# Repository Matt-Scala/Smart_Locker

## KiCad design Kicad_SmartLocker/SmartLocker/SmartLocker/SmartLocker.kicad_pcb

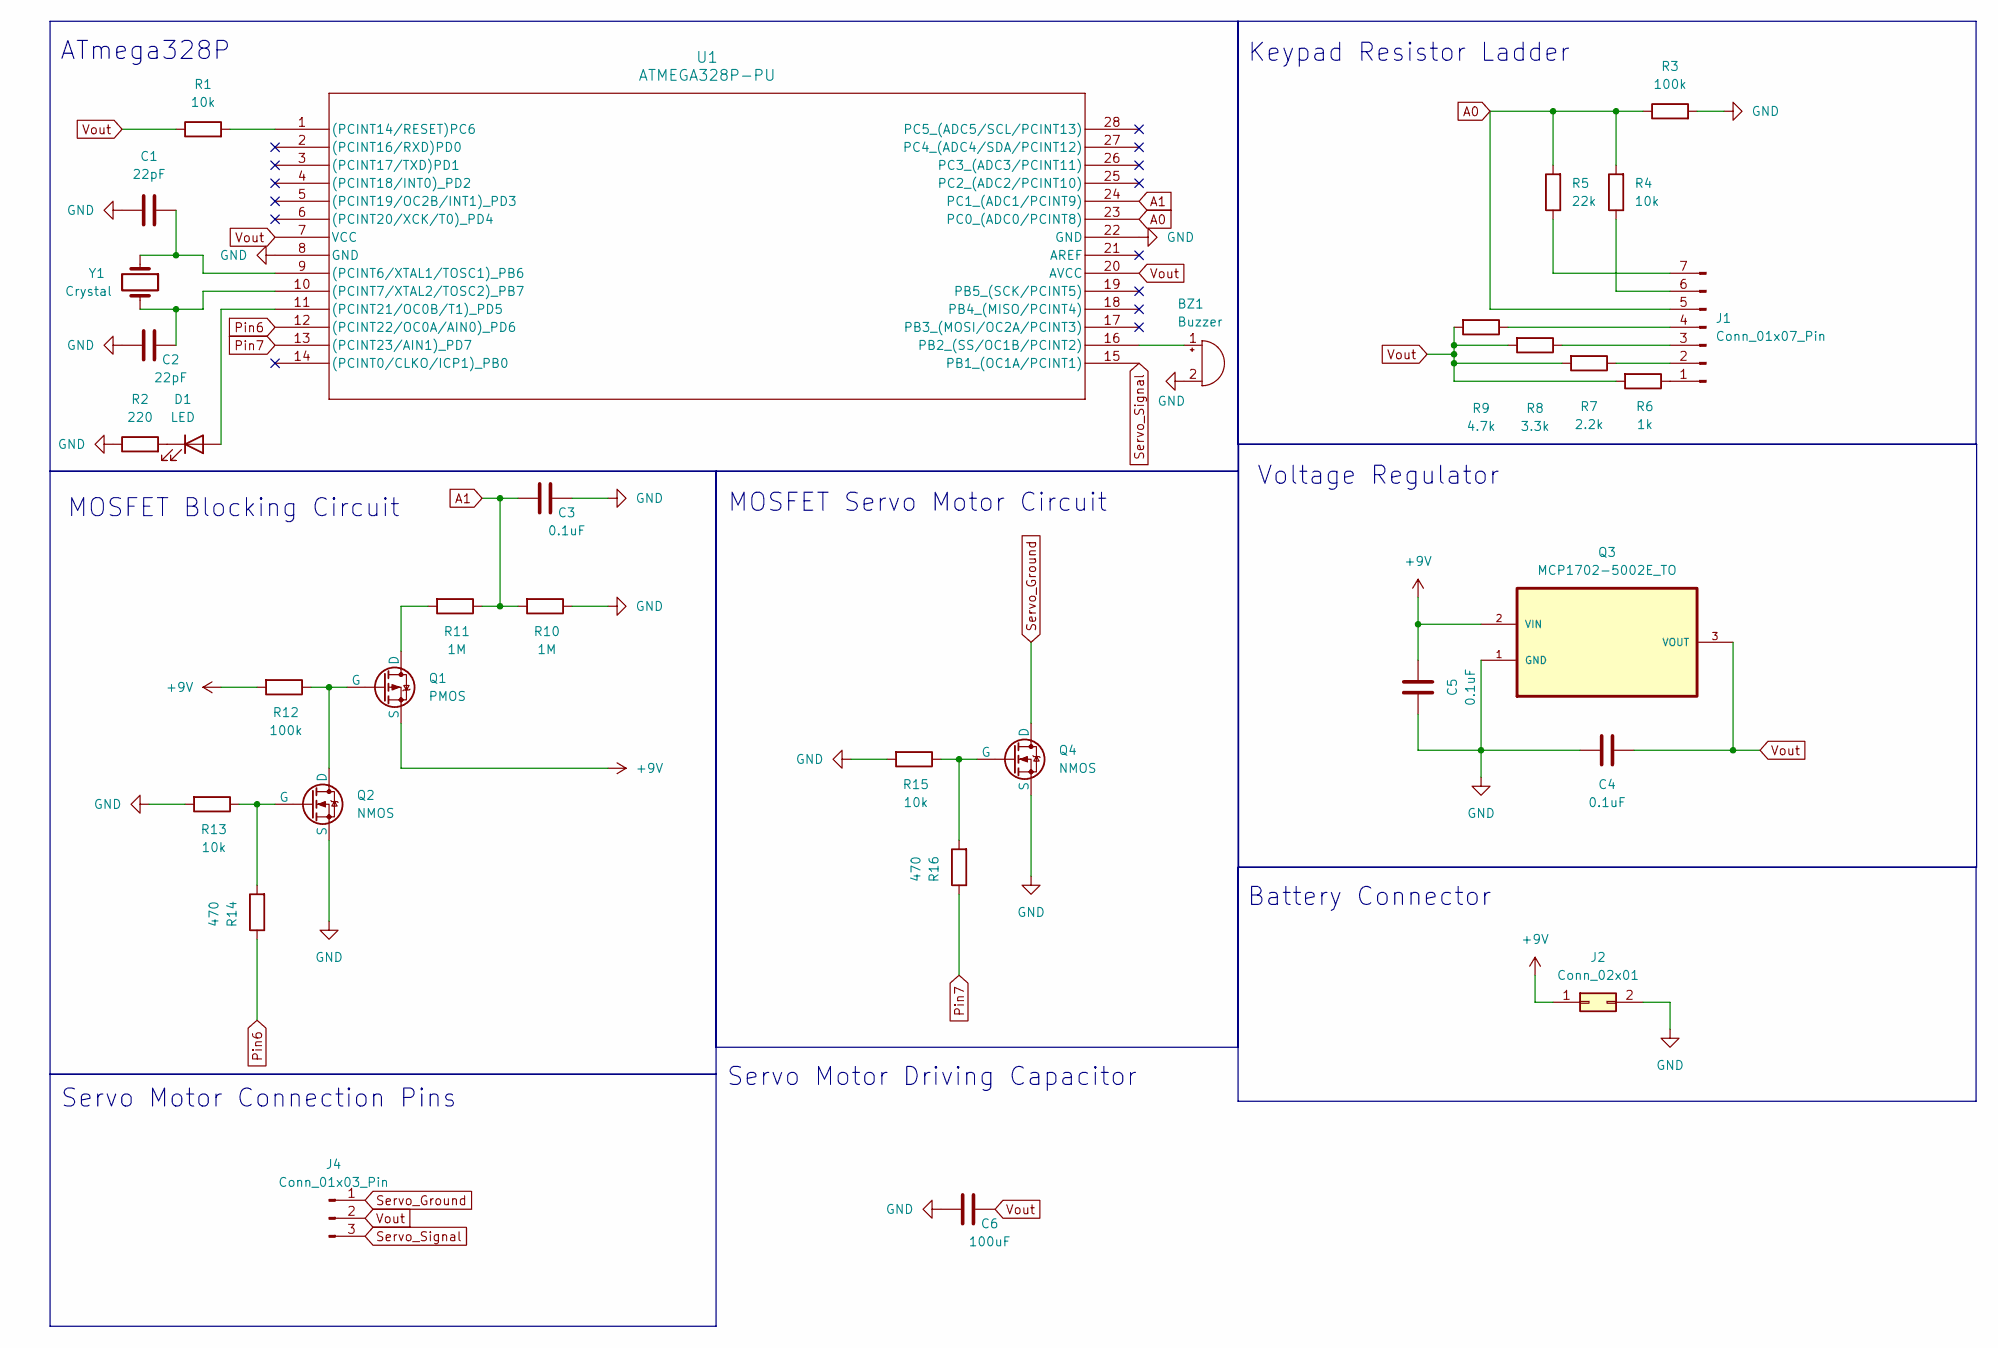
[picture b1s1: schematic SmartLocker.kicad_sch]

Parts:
BZ1: Buzzer; CUI_CMI-1275C-050
C1, C2: 22pF; C_Disc_D4.3mm_W1.9mm_P5.00mm_Handsolder
C3, C4, C5: 0.1uF; C_Disc_D4.3mm_W1.9mm_P5.00mm_Handsolder
C6: 100uF; C_Radial_D8.0mm_H7.0mm_P3.50mm
D1: LED; LED_D3.0mm
J1: Conn_01x07_Pin; PinSocket_1x07_P2.54mm_Vertical
J2: Conn_02x01; BatteryConnector
J4: Conn_01x03_Pin; PinSocket_1x03_P2.54mm_Vertical
Q1: PMOS; TO-92_HandSolder
Q2, Q4: NMOS; TO-92_HandSolder
Q3: MCP1702-5002E_TO; MCP1702 TO-92; MPN MCP1702-5002E/TO
R1, R4, R13, R15: 10k; R_Axial_DIN0309_L9.0mm_D3.2mm_P12.70mm_Horizontal
R2: 220; R_Axial_DIN0309_L9.0mm_D3.2mm_P12.70mm_Horizontal
R3, R12: 100k; R_Axial_DIN0309_L9.0mm_D3.2mm_P12.70mm_Horizontal
R5: 22k; R_Axial_DIN0309_L9.0mm_D3.2mm_P12.70mm_Horizontal
R6: 1k; R_Axial_DIN0309_L9.0mm_D3.2mm_P12.70mm_Horizontal
R7: 2.2k; R_Axial_DIN0309_L9.0mm_D3.2mm_P12.70mm_Horizontal
R8: 3.3k; R_Axial_DIN0309_L9.0mm_D3.2mm_P12.70mm_Horizontal
R9: 4.7k; R_Axial_DIN0309_L9.0mm_D3.2mm_P12.70mm_Horizontal
R10, R11: 1M; R_Axial_DIN0207_L6.3mm_D2.5mm_P10.16mm_Horizontal
R14, R16: 470; R_Axial_DIN0207_L6.3mm_D2.5mm_P10.16mm_Horizontal
U1: ATMEGA328P-PU; ATmega328P
Y1: Crystal; Crystal_HC49-4H_Vertical

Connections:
+9V: C5.2, J2.1, Q1.3 (S), Q3.2 (VIN), R12.2
A0: J1.5, R3.1, R4.2, R5.2, U1.23 (PC0_(ADC0/PCINT8))
A1: C3.1, R10.2, R11.1, U1.24 (PC1_(ADC1/PCINT9))
GND: BZ1.2 (-), C1.1, C2.1, C3.2, C4.1, C5.1, C6.1, J2.2, Q2.3 (S), Q3.1 (GND), Q4.3 (S), R2.1, R3.2, R10.1, R13.2, R15.2, U1.8 (GND), U1.22 (GND)
unnamed: BZ1.1 (+), U1.16 (PB2_(SS/OC1B/PCINT2))
unnamed: D1.2 (A), U1.11 ((PCINT21/OC0B/T1)_PD5)
unnamed: D1.1 (K), R2.2
unnamed: J1.1, R6.1
unnamed: J1.2, R7.1
unnamed: J1.3, R8.1
unnamed: J1.4, R9.1
unnamed: J1.6, R4.1
unnamed: J1.7, R5.1
unnamed: Q1.1 (D), R11.2
unnamed: Q1.2 (G), Q2.1 (D), R12.1
unnamed: Q2.2 (G), R13.1, R14.2
unnamed: Q4.2 (G), R15.1, R16.2
unnamed: C1.2, U1.9 ((PCINT6/XTAL1/TOSC1)_PB6), Y1.1
unnamed: C2.2, U1.10 ((PCINT7/XTAL2/TOSC2)_PB7), Y1.2
unnamed: R1.2, U1.1 ((PCINT14/RESET)PC6)
Pin6: R14.1, U1.12 ((PCINT22/OC0A/AIN0)_PD6)
Pin7: R16.1, U1.13 ((PCINT23/AIN1)_PD7)
Servo_Ground: J4.1, Q4.1 (D)
Servo_Signal: J4.3, U1.15 (PB1_(OC1A/PCINT1))
Vout: C4.2, C6.2, J4.2, Q3.3 (VOUT), R1.1, R6.2, R7.2, R8.2, R9.2, U1.7 (VCC), U1.20 (AVCC)

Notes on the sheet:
Voltage Regulator
MOSFET Servo Motor Circuit
ATmega328P
Keypad Resistor Ladder
MOSFET Blocking Circuit
Servo Motor Driving Capacitor
Servo Motor Connection Pins
Battery Connector

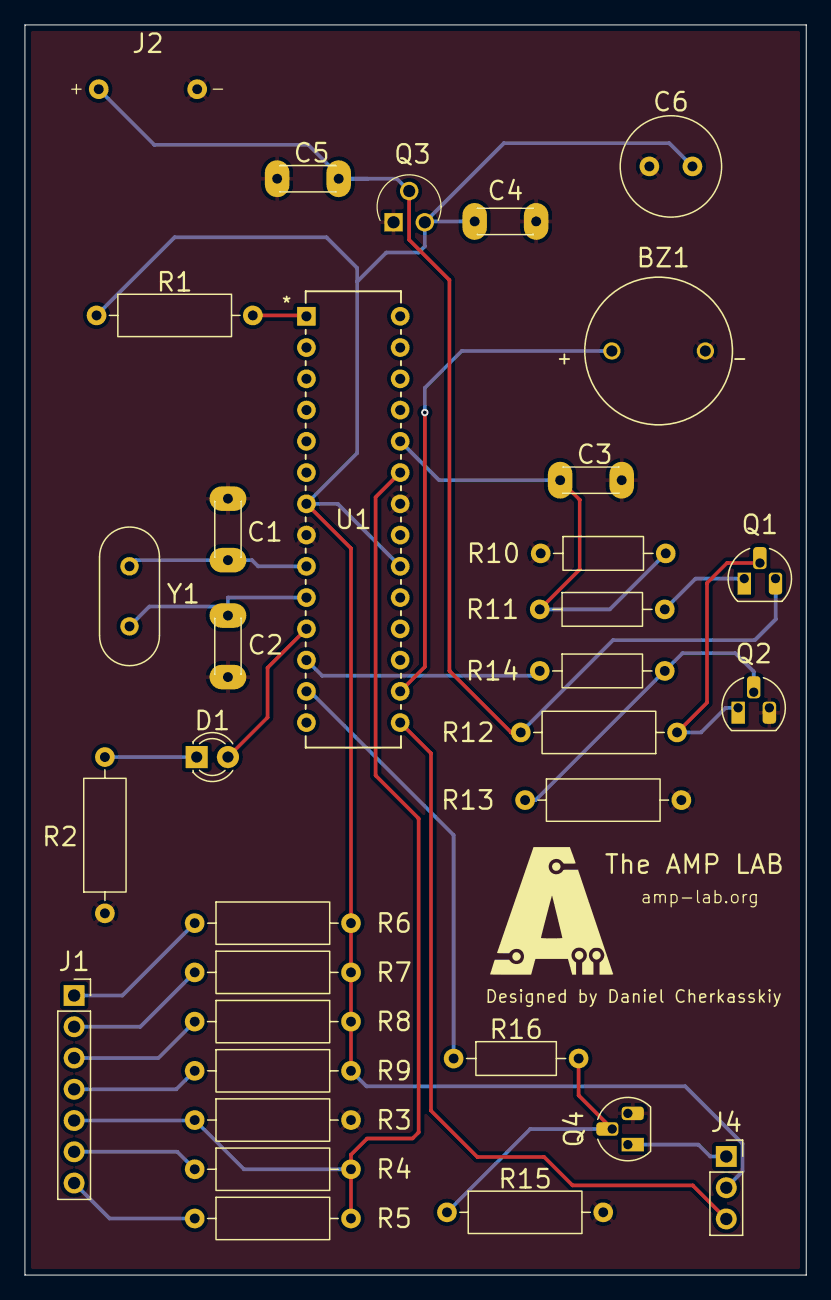
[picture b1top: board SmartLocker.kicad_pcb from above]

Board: 2 copper layers, 63.5 x 101.6 mm, 33 parts (0 on the bottom side), 25 nets.

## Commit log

2026-05-07 PCB_Smart_Locker
2026-05-07 Other_Smart_Locker_Files
2026-05-07 more
2026-05-07 done_1st_var
2026-05-07 more_changes
2026-05-07 logos
2026-05-07 quarter_inch_latch
2026-05-07 more_changes_continued
2026-05-07 production_files
2026-05-08 updates_1
2026-05-08 update1_print_changes
    Joel_print_this
